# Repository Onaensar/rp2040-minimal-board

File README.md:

# ⚡ MDC RP2040 - Custom 4-Layer Development Board

A compact, industrial-standard 4-layer custom microcontroller development board powered by the **Raspberry Pi RP2040**. Built for high signal integrity, low-noise power distribution, and full hardware ESD protection.

---

## 📸 Hardware Overview

| Top View | Bottom View |
| :---: | :---: |
|  |  |

---

## 🛠 Key Hardware Specifications

* **Microcontroller:** Raspberry Pi RP2040 (Dual ARM Cortex-M0+ @ 133 MHz, 264 KB SRAM)
* **Flash Memory:** 16 MB (128 Mb) Winbond QSPI Flash (`W25Q128JVSIQ`)
* **Power Regulation:**
  * High-performance 600 mA 3.3V LDO regulator (`AP2112K-3.3`)
  * Low ESR ceramic decoupling network across all internal power rails (`DVDD 1.1V`, `IOVDD 3.3V`, `ADC_AVDD 3.3V`)
* **USB Interface:** USB Type-C 2.0 with dedicated ESD protection (`USBLC6-2SC6`) and dual 5.1 kΩ CC configuration resistors
* **Clock System:** 12 MHz surface-mount crystal oscillator with dedicated symmetrical load capacitor array (`27 pF`) and isolated ground shielding
* **I/O & Peripherals:**
  * Standard 2.54 mm dual-row pinout exposing 30 multi-function GPIOs (SPI, I2C, UART, PWM, ADC)
  * Dedicated 3-pin SWD interface (`SWCLK`, `SWDIO`, `GND`) for debug probes (Picoprobe / J-Link)
  * Hardware `BOOT` and `RESET` pushbuttons
  * Status LEDs for `Power` (+3.3V) and user-programmable indicator (`GPIO25`)

---

## 📐 PCB Layer Stack-up (4-Layer FR-4)

Designed adhering to standard 1.6 mm PCB manufacturing guidelines (e.g., JLCPCB JLC04161H / PCBWay):

| Layer | Type | Copper Thickness | Function / Allocation |
| :--- | :--- | :--- | :--- |
| **Layer 1 (F.Cu)** | Signal | 1.0 oz (35 µm) | Core ICs, high-speed USB differential pairs, QSPI routing, and local decoupling loops |
| **Layer 2 (In1.Cu)** | Plane | 0.5 oz (17.5 µm) | **Unbroken Solid Ground Plane (GND)** for optimal return path and EMI shielding |
| **Layer 3 (In2.Cu)** | Power | 0.5 oz (17.5 µm) | Dedicated **+3.3V & +1.1V Power Planes** |
| **Layer 4 (B.Cu)** | Signal / GND | 1.0 oz (35 µm) | Low-speed signal breakout paths with unbroken ground copper pour |

---

## 📁 Repository Structure

```text
├── docs/                   # Renderings, hardware design schematics (PDF), and pinout guides
│   └── images/             # 3D PCB board renders
├── hardware/               # KiCad project files (.kicad_pro, .kicad_sch, .kicad_pcb)
├── manufacturing/          # Production-ready Gerbers, Drill files, BOM, and CPL files
├── .gitignore              # KiCad workspace exclusion rules
└── README.md

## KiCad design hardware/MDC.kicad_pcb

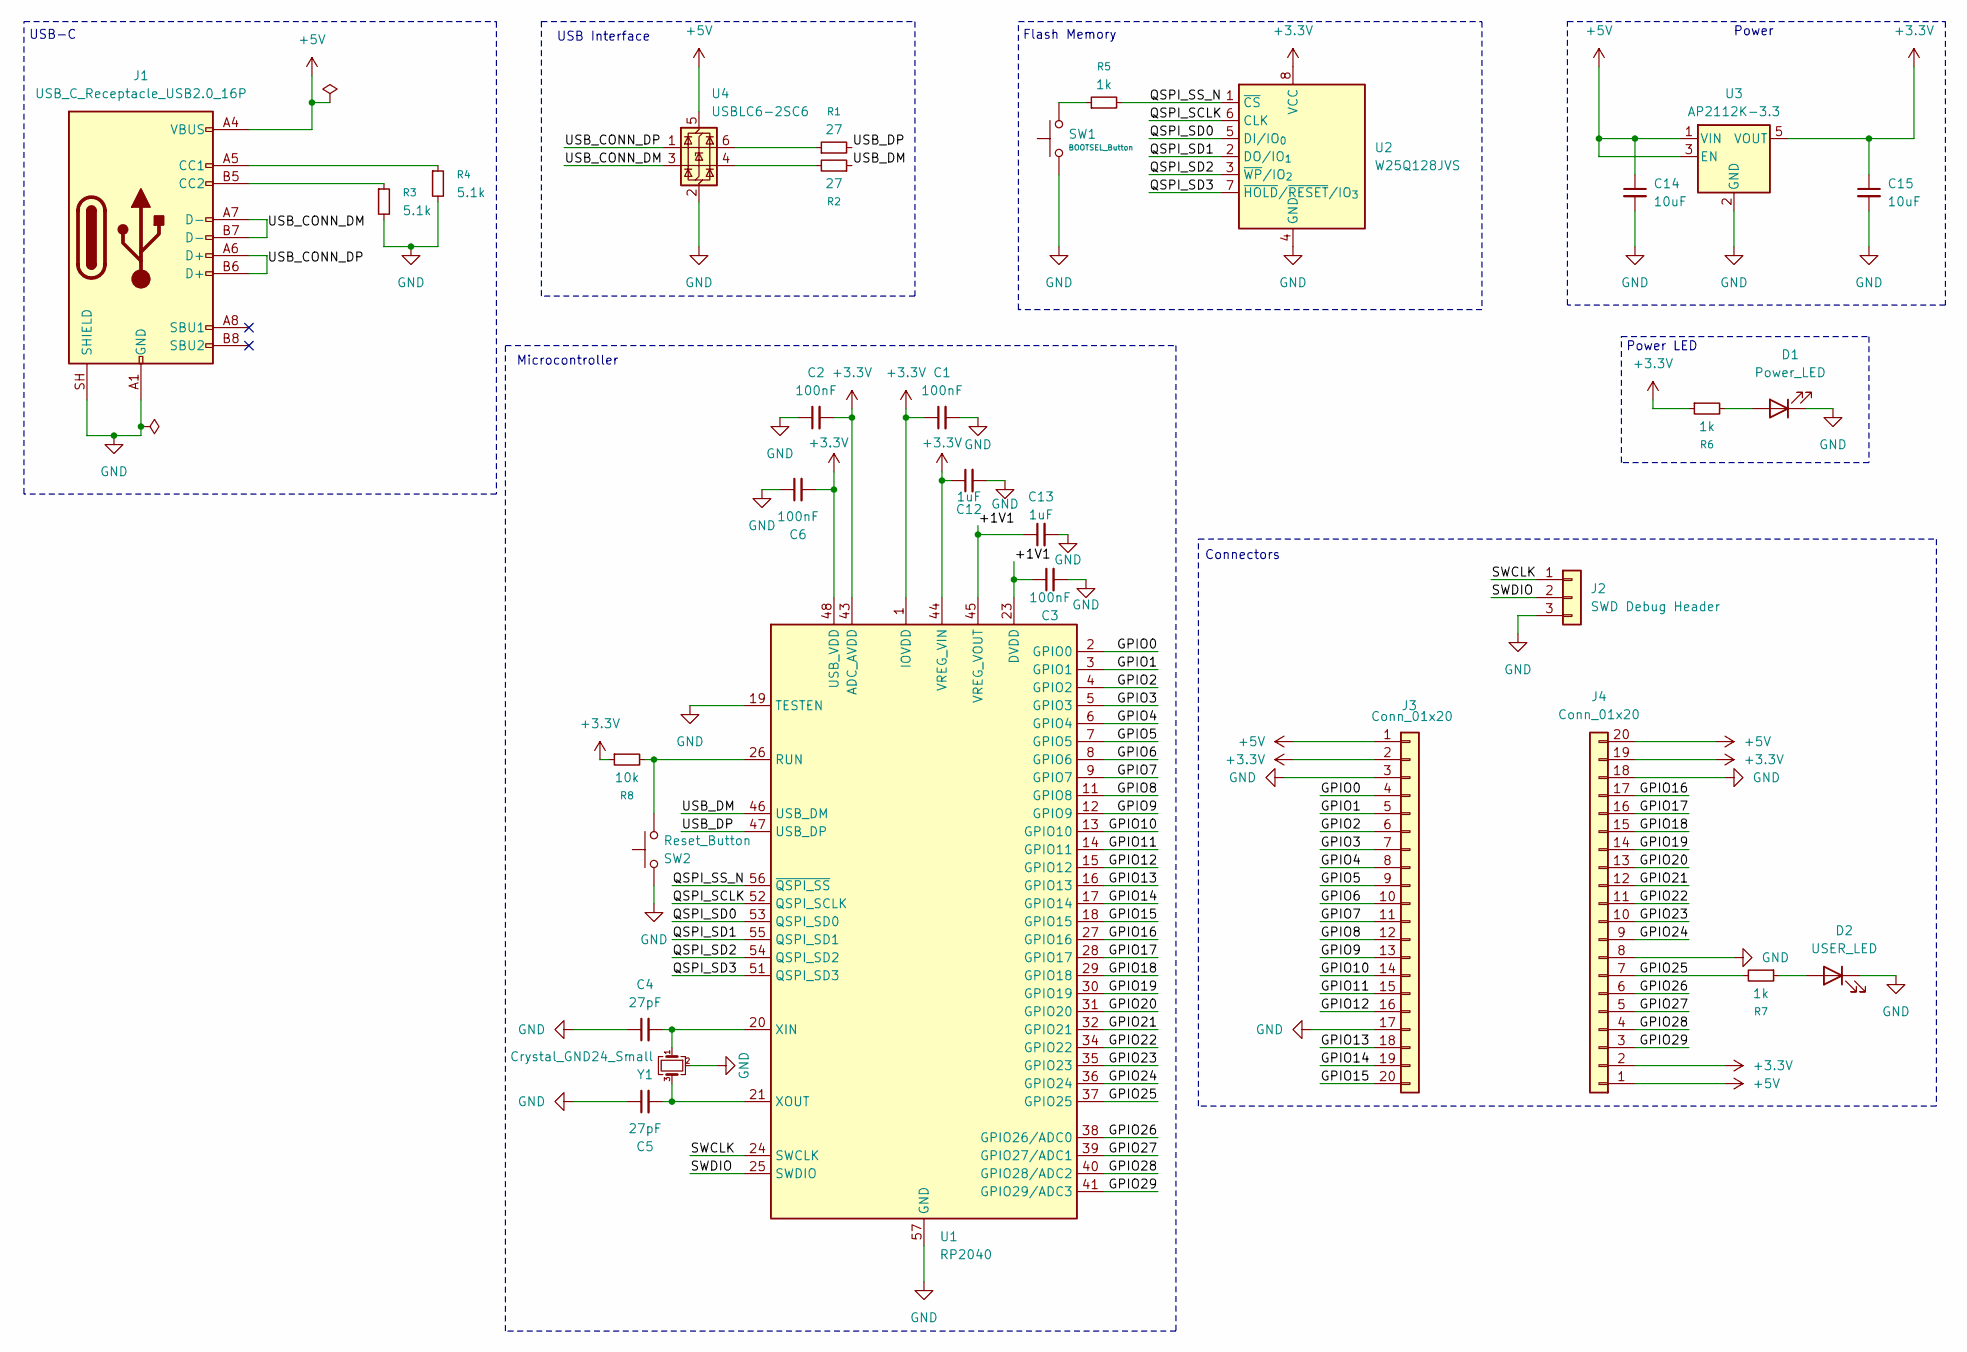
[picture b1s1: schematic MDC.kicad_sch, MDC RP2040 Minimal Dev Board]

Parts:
C1, C2, C3, C6: 100nF; C_0603_1608Metric
C4, C5: 27pF; C_0603_1608Metric
C12, C13: 1uF; C_0603_1608Metric
C14, C15: 10uF; C_0603_1608Metric
D1: Power_LED; LED_0603_1608Metric
D2: USER_LED; LED_0603_1608Metric
J1: USB_C_Receptacle_USB2.0_16P; USB_C_Receptacle_GCT_USB4105-xx-A_16P_TopMnt_Horizontal
J2: SWD Debug Header; PinHeader_1x03_P2.54mm_Vertical
J3, J4: Conn_01x20; PinHeader_1x20_P2.54mm_Vertical
R1, R2: 27; R_0603_1608Metric
R3, R4: 5.1k; R_0603_1608Metric
R5, R6, R7: 1k; R_0603_1608Metric
R8: 10k; R_0603_1608Metric
SW1: BOOTSEL_Button; SW_SPST_TL3342
SW2: Reset_Button; SW_SPST_TL3342
U1: RP2040; QFN-56-1EP_7x7mm_P0.4mm_EP3.2x3.2mm
U2: W25Q128JVS; SOIC-8_5.3x5.3mm_P1.27mm
U3: AP2112K-3.3; SOT-23-5
U4: USBLC6-2SC6; SOT-23-6
Y1: Crystal_GND24_Small; Crystal_SMD_3225-4Pin_3.2x2.5mm

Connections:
+3.3V: C1.1, C2.2, C6.2, C12.1, C15.1, J3.2, J4.2, J4.19, R6.1, R8.1, U1.1 (IOVDD), U1.10 (IOVDD), U1.22 (IOVDD), U1.33 (IOVDD), U1.42 (IOVDD), U1.43 (ADC_AVDD), U1.44 (VREG_VIN), U1.48 (USB_VDD), U1.49 (IOVDD), U2.8 (VCC), U3.5 (VOUT)
+5V: C14.1, J1.A4 (VBUS), J1.A9 (VBUS), J1.B4 (VBUS), J1.B9 (VBUS), J3.1, J4.1, J4.20, U3.1 (VIN), U3.3 (EN), U4.5 (VBUS)
/+1V1: C3.1, C13.1, U1.23 (DVDD), U1.45 (VREG_VOUT), U1.50 (DVDD)
/GPIO0: J3.4, U1.2 (GPIO0)
/GPIO1: J3.5, U1.3 (GPIO1)
/GPIO2: J3.6, U1.4 (GPIO2)
/GPIO3: J3.7, U1.5 (GPIO3)
/GPIO4: J3.8, U1.6 (GPIO4)
/GPIO5: J3.9, U1.7 (GPIO5)
/GPIO6: J3.10, U1.8 (GPIO6)
/GPIO7: J3.11, U1.9 (GPIO7)
/GPIO8: J3.12, U1.11 (GPIO8)
/GPIO9: J3.13, U1.12 (GPIO9)
/GPIO10: J3.14, U1.13 (GPIO10)
/GPIO11: J3.15, U1.14 (GPIO11)
/GPIO12: J3.16, U1.15 (GPIO12)
/GPIO13: J3.18, U1.16 (GPIO13)
/GPIO14: J3.19, U1.17 (GPIO14)
/GPIO15: J3.20, U1.18 (GPIO15)
/GPIO16: J4.17, U1.27 (GPIO16)
/GPIO17: J4.16, U1.28 (GPIO17)
/GPIO18: J4.15, U1.29 (GPIO18)
/GPIO19: J4.14, U1.30 (GPIO19)
/GPIO20: J4.13, U1.31 (GPIO20)
/GPIO21: J4.12, U1.32 (GPIO21)
/GPIO22: J4.11, U1.34 (GPIO22)
/GPIO23: J4.10, U1.35 (GPIO23)
/GPIO24: J4.9, U1.36 (GPIO24)
/GPIO25: J4.7, R7.2, U1.37 (GPIO25)
/GPIO26: J4.6, U1.38 (GPIO26/ADC0)
/GPIO27: J4.5, U1.39 (GPIO27/ADC1)
/GPIO28: J4.4, U1.40 (GPIO28/ADC2)
/GPIO29: J4.3, U1.41 (GPIO29/ADC3)
/QSPI_SCLK: U1.52 (QSPI_SCLK), U2.6 (CLK)
/QSPI_SD0: U1.53 (QSPI_SD0), U2.5 (DI/IO_{0})
/QSPI_SD1: U1.55 (QSPI_SD1), U2.2 (DO/IO_{1})
/QSPI_SD2: U1.54 (QSPI_SD2), U2.3 (~WP/IO_{2})
/QSPI_SD3: U1.51 (QSPI_SD3), U2.7 (~HOLD/~RESET/IO_{3})
/QSPI_SS_N: R5.2, U1.56 (~QSPI_SS), U2.1 (~CS)
/SWCLK: J2.1, U1.24 (SWCLK)
/SWDIO: J2.2, U1.25 (SWDIO)
/USB_CONN_DM: J1.A7 (D-), J1.B7 (D-), U4.3 (I/O2)
/USB_CONN_DP: J1.A6 (D+), J1.B6 (D+), U4.1 (I/O1)
/USB_DM: R2.1, U1.46 (USB_DM)
/USB_DP: R1.2, U1.47 (USB_DP)
GND: C1.2, C2.1, C3.2, C4.1, C5.1, C6.1, C12.2, C13.2, C14.2, C15.2, D1.1 (K), D2.1 (K), J1.A1 (GND), J1.A12 (GND), J1.B1 (GND), J1.B12 (GND), J1.SH (SHIELD), J2.3, J3.3, J3.17, J4.8, J4.18, R3.2, R4.2, SW1.1, SW2.2, U1.19 (TESTEN), U1.57 (GND), U2.4 (GND), U3.2 (GND), U4.2 (GND), Y1.2 (G), Y1.4 (G)
unnamed: D1.2 (A), R6.2
unnamed: D2.2 (A), R7.1
unnamed: J1.A5 (CC1), R4.1
unnamed: J1.B5 (CC2), R3.1
unnamed: R1.1, U4.6 (I/O1)
unnamed: R2.2, U4.4 (I/O2)
unnamed: R5.1, SW1.2
unnamed: R8.2, SW2.1, U1.26 (RUN)
unnamed: C4.2, U1.20 (XIN), Y1.1
unnamed: C5.2, U1.21 (XOUT), Y1.3

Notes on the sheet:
Power
Connectors
Flash Memory
USB-C
Power LED
Microcontroller
USB Interface

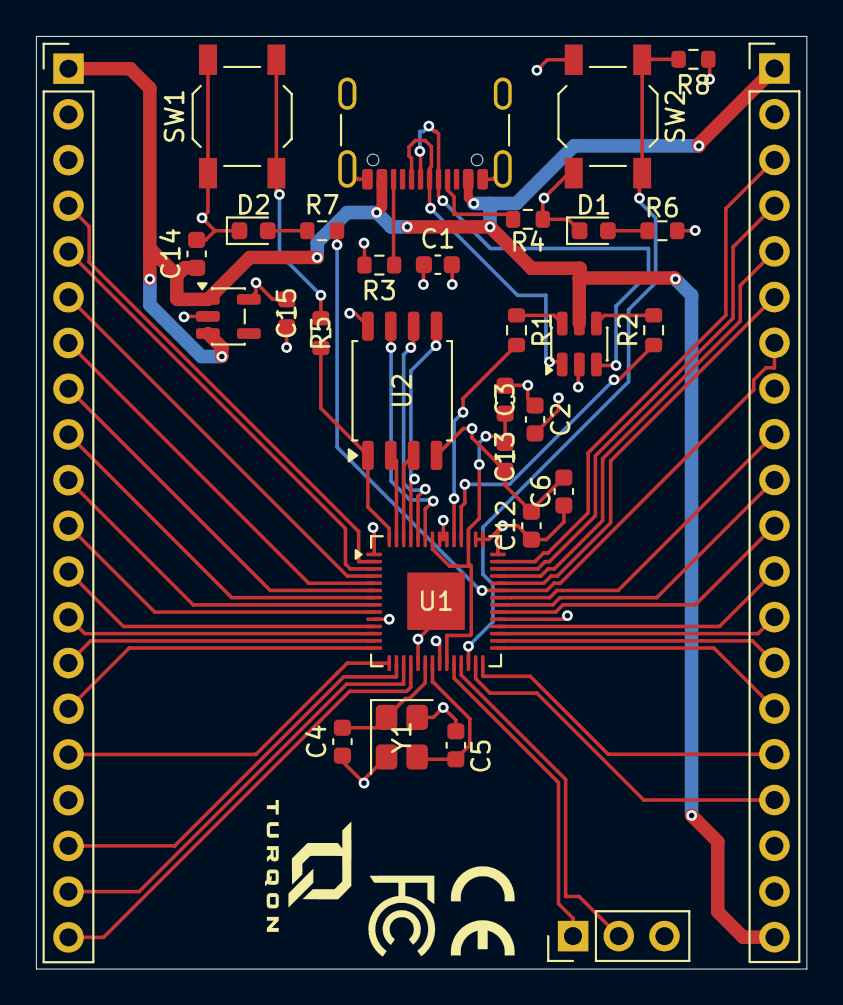
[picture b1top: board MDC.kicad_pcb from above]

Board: 4 copper layers, 42.8 x 51.8 mm, 31 parts (0 on the bottom side), 56 nets.
